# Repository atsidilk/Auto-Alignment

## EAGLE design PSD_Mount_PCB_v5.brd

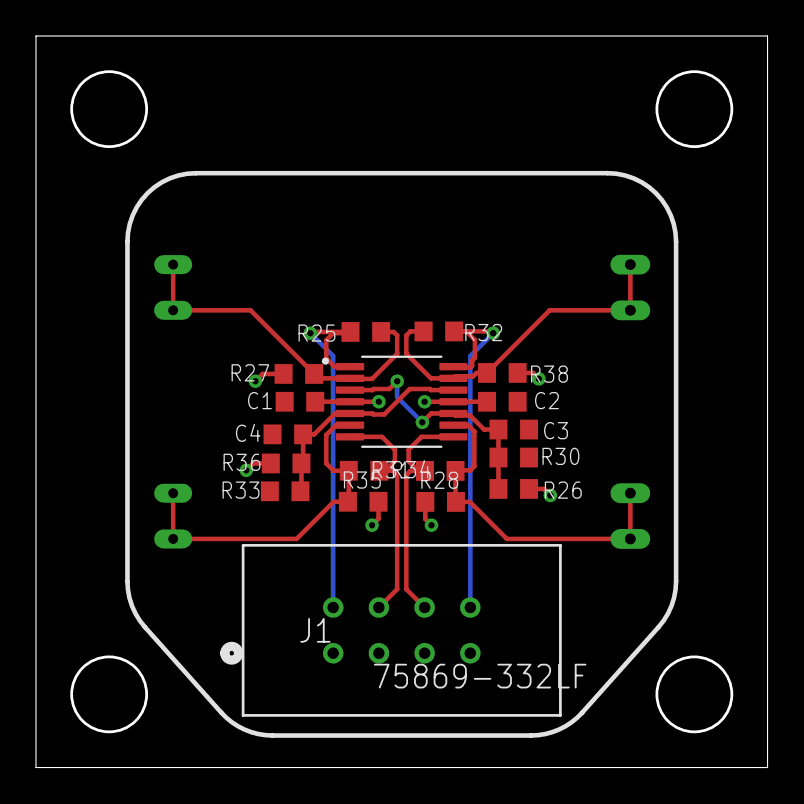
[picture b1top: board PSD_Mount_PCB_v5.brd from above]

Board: 4 copper layers, 40.5 x 40.5 mm, 19 parts (1 on the bottom side), 13 nets.

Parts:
AMP1: OPA4140; SOP65P640X120-14N
C1, C2, C3, C4: 0603
J1: 75869-332LF; CONN_332LF_AMP
R25, R26, R27, R28, R30, R31, R32, R33, R34, R35, R36, R38: 0603
U$1: 2L10UV_SU7

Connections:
15V: AMP1.4, C1.2, J1.7, R35.1, R36.1, R38.1
-15V: AMP1.11, C2.2, J1.3, R26.2, R27.2, R28.2
BIASX: AMP1.5, AMP1.12, C4.2, R33.2, R36.2
BIASY: AMP1.3, AMP1.10, C3.2, R26.1, R30.2
GND: C1.1, C2.1, C3.1, C4.1, J1.1, J1.5, R30.1, R33.1
X1: AMP1.6, R34.1, R35.2, U$1.X1-1, U$1.X1-2
X1_OUT: AMP1.7, J1.4, R34.2
X2: AMP1.13, R32.2, R38.2, U$1.X2-1, U$1.X2-2
X2_OUT: AMP1.14, J1.8, R32.1
Y1: AMP1.2, R25.1, R27.1, U$1.Y1-1, U$1.Y1-2
Y1_OUT: AMP1.1, J1.2, R25.2
Y2: AMP1.9, R28.1, R31.1, U$1.Y2-1, U$1.Y2-2
Y2_OUT: AMP1.8, J1.6, R31.2

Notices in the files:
parts and their libraries:
COPYRIGHT: Copyright (C) 2018 Accelerated Designs. All rights reserved
